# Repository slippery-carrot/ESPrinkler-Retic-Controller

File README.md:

# 🌱 ESPrinkler Retic Controller

An open-source, ESP32-based smart irrigation controller built with **ESPHome** and designed for seamless integration with **Home Assistant**.

ESPrinkler gives you full local control over your irrigation system—no cloud services, no subscriptions, and no reliance on external servers. All schedules are stored directly on the device, ensuring your system continues to run even if Home Assistant or network connectivity becomes unavailable.

---

## 🚀 Features

- Fully local operation (no cloud dependencies)  
- Home Assistant integration via ESPHome  
- Standalone operation with onboard schedule storage  
- Solid-state design with optically isolated outputs  
- Control up to **8 irrigation zones + pump/master valve**  
- Support for **up to 3 independent watering programs**  
- Flexible scheduling:
  - Day-of-week control  
  - Up to 4 start times per program  
  - Configurable zone durations and repeat cycles  
- LED indicators for system status and outputs  

---

## 🧠 How It Works

ESPrinkler operates using up to **three independent watering programs**, each of which defines:

- When watering occurs (days + start times)  
- Which zones are active  
- How long each zone runs  
- Whether the cycle repeats  

All configuration is done through **Home Assistant entities**, and once configured, the controller runs autonomously.

⚠️ Programs **do not prevent overlap automatically**, so you must ensure schedules don’t conflict.

---

## 🏗️ Hardware Overview

The controller is built around an **ESP32 (ESP32-DevKitC compatible)** and a custom PCB designed for irrigation control.

Key hardware characteristics:

- Compatible with 24VAC reticulation systems
- Solid-state solenoid switching  
- Isolated AC/DC sections
- Fused solenoid power output
- Terminal block wiring for:
  - Power input  
  - Pump/master valve  
  - 8 irrigation zones  
- Optional external LEDs for:
  - Wi-Fi status  
  - System status  

For full specifications, wiring diagrams, and pinouts, see:  
**[Hardware Specifications Wiki](../../wiki/Hardware-Specifications)**

---

## ⚡ Requirements

To build and use ESPrinkler, you’ll need:

- ESP32 Dev Board (ESP32-DevKitC compatible)  
- ESPrinkler PCB (assembled or DIY)  
- 24VAC transformer (~30VA recommended)  
- Fuse (M205 1A Quick Blow)  
- Suitable enclosure  
- Wiring/connectors for your installation  
- Home Assistant with ESPHome installed  

---

## 🛠️ Getting Started

### 1. Set Up ESPHome

Install and configure ESPHome in Home Assistant:  
https://esphome.io/guides/getting_started_hassio/

---

### 2. Prepare Firmware

- Copy the provided `secrets.yaml` values into your ESPHome setup  
- Import the `retic-controller.yaml` file into ESPHome (Add new device -> Import from file) 
- Update the substitutions (Wi-Fi, API key, device name, etc.)  

---

### 3. Flash the Device

- Click the 3 dots under the new configuration
- Click "install" and follow your preferred method to flash your ESP32
- I recommend choosing "manual download" and then navigate to [ESPHome Web](https://web.esphome.io/) to flash your device using the binary file
- Once flashed, the device will appear in Home Assistant

---

### 4. Wire the Hardware

- Connect 24VAC input  
- Connect solenoids (zones + common)  
- Install fuse  
- Optional: connect status LEDs  

⚠️ **Warning:** This involves working with mains/low-voltage AC systems. Follow all relevant electrical safety standards and regulations.
👉 See the **[Hardware Specifications Wiki](../../wiki/Hardware-Specifications)** for full wiring details and pinouts.

---

### 5. Configure in Home Assistant

Once the device is online:

- Enable one or more programs  
- Set watering days  
- Configure start times  
- Enable zones and durations
- An example [dashboard page .yaml file](https://github.com/slippery-carrot/ESPrinkler-Retic-Controller/blob/main/ESPHome/ESPrinkler_Dashboard_Example.yaml) has been provided as an example layout in Home Assistant

⚠️ **NOTE:** The example dashboard yaml uses [Mushroom Cards](https://github.com/piitaya/lovelace-mushroom), so make sure to install that if you want it to function.
👉 See the **[Home Assistant Entities Wiki](../../wiki/Home-Assistant-Entities)** for a full breakdown of all controls, sensors, and configuration options.

---

## 🌿 Program Basics

Each program requires:

- ✅ Program enabled  
- ✅ At least one watering day  
- ✅ At least one start time  
- ✅ At least one active zone with duration  

Optional settings:

- Repeat cycles (repeat full zone sequence)  

---

## 🏠 Home Assistant Integration

ESPrinkler exposes a full set of:

- **Controls** (start/stop, enable program, pause)  
- **Sensors** (current zone, time remaining, next cycle)  
- **Configuration entities** (days, times, durations, repeats)  
- **Diagnostics** (Wi-Fi signal, uptime, firmware, etc.)  

👉 Full details here:  
**[Home Assistant Entities Wiki](../../wiki/Home-Assistant-Entities)**

---

## 🧩 Project Structure

- Firmware: ESPHome YAML configuration and secrets example, including example dashboard layout  
- Hardware: Custom PCB design in KiCad and production files
- Documentation:
  - README (this file)  
  - Hardware Wiki  
  - Home Assistant Wiki  

---

## ⚠️ Important Notes

- Programs **can overlap** if configured incorrectly—this is not automatically prevented  
- Default start times may be active—always verify configuration  
- Ensure the transformer you choose is correctly sized for your solenoid load
- Always use appropriate fuse protection

---

## 🪰 Limitations, Issues, and Bugs
 - ESPrinkler requires connection to home assistant at least once in order to set its internal clock. Without this, it has no reference to the current time and date

## 🔗 Documentation

- 📘 **[Hardware Specifications Wiki](../../wiki/Hardware-Specifications)** – Pinouts, wiring, electrical specs  
- 📗 **[Home Assistant Entities Wiki](../../wiki/Home-Assistant-Entities)** – Entities, controls, automation  

---

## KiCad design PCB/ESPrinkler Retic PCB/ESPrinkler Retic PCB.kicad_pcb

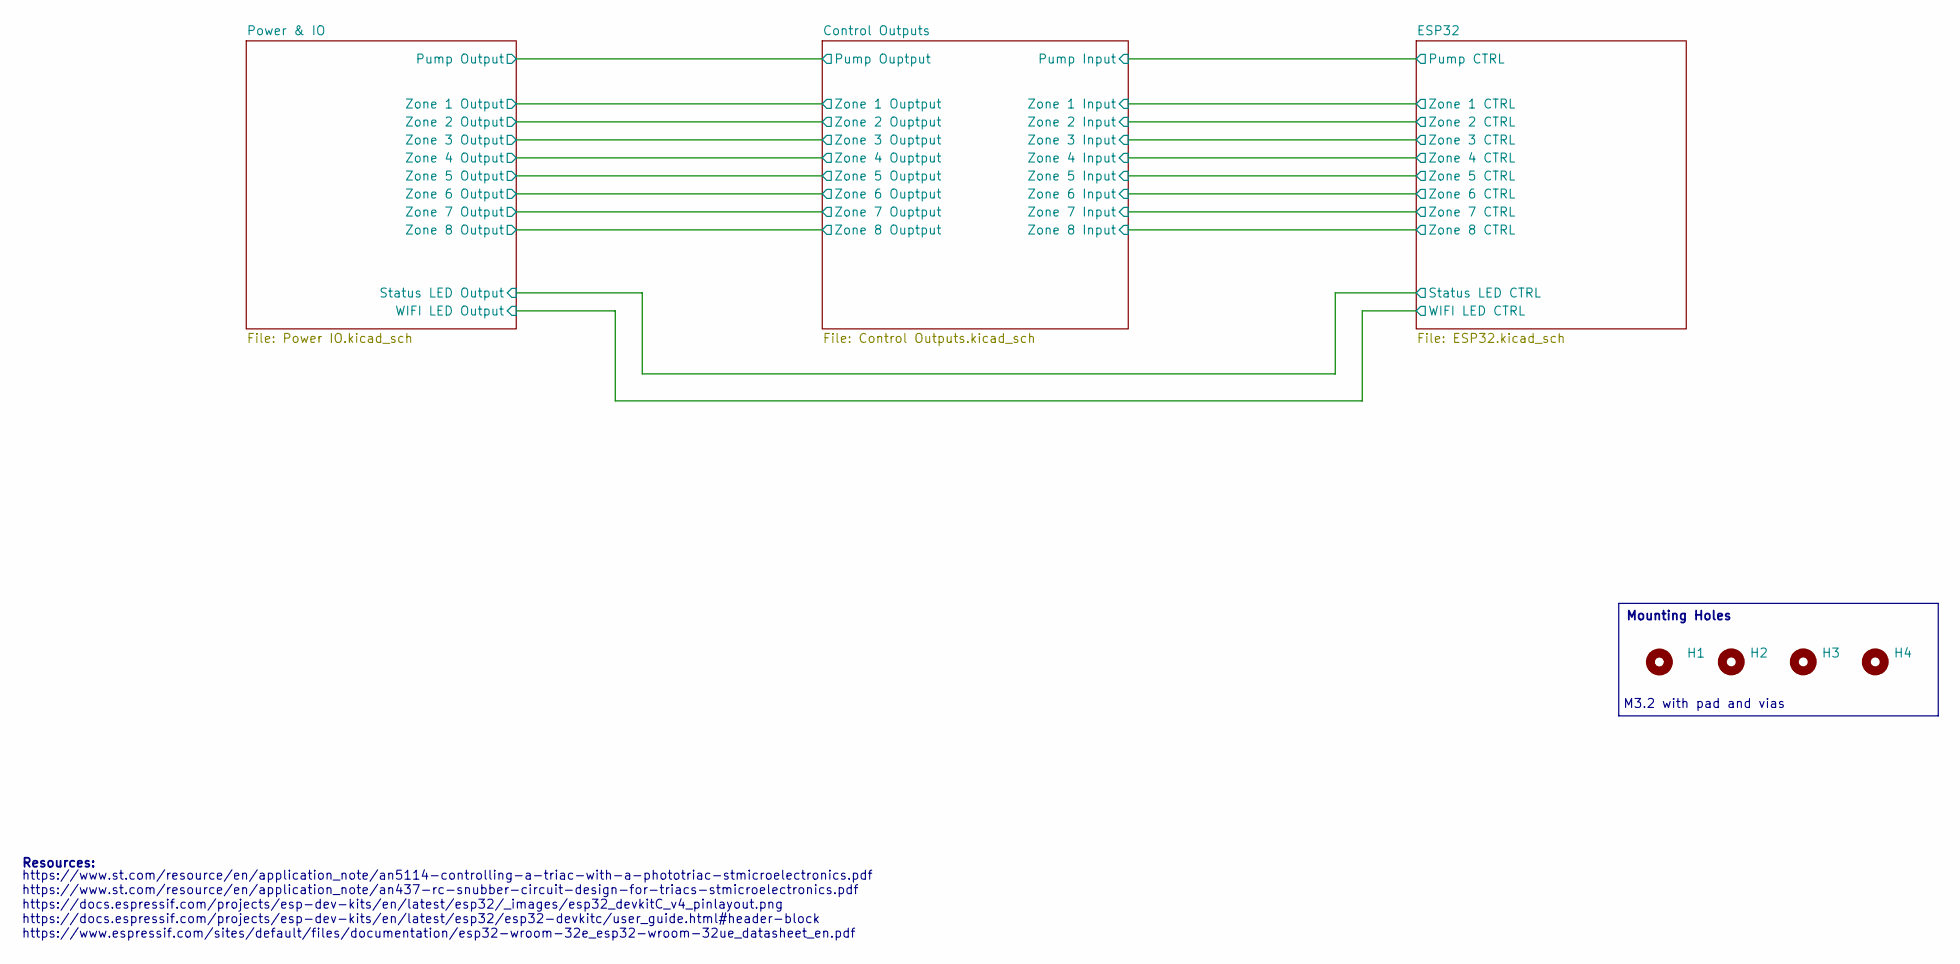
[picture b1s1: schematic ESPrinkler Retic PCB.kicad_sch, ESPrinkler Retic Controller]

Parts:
H1, H2, H3, H4: MountingHole; MountingHole_3.2mm_M3_Pad_Via

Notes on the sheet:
https://www.st.com/resource/en/application_note/an5114-controlling-a-triac-with-a-phototriac-stmicroelectronics.pdf https://www.st.com/resource/en/application_note/an437-rc-snubber-circuit-design-for-triacs-stmicroelectronics.pdf https://docs.espressif.com/projects/esp-dev-kits/en/latest/esp32/_ima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
M3.2 with pad and vias
Resources:
Mounting Holes

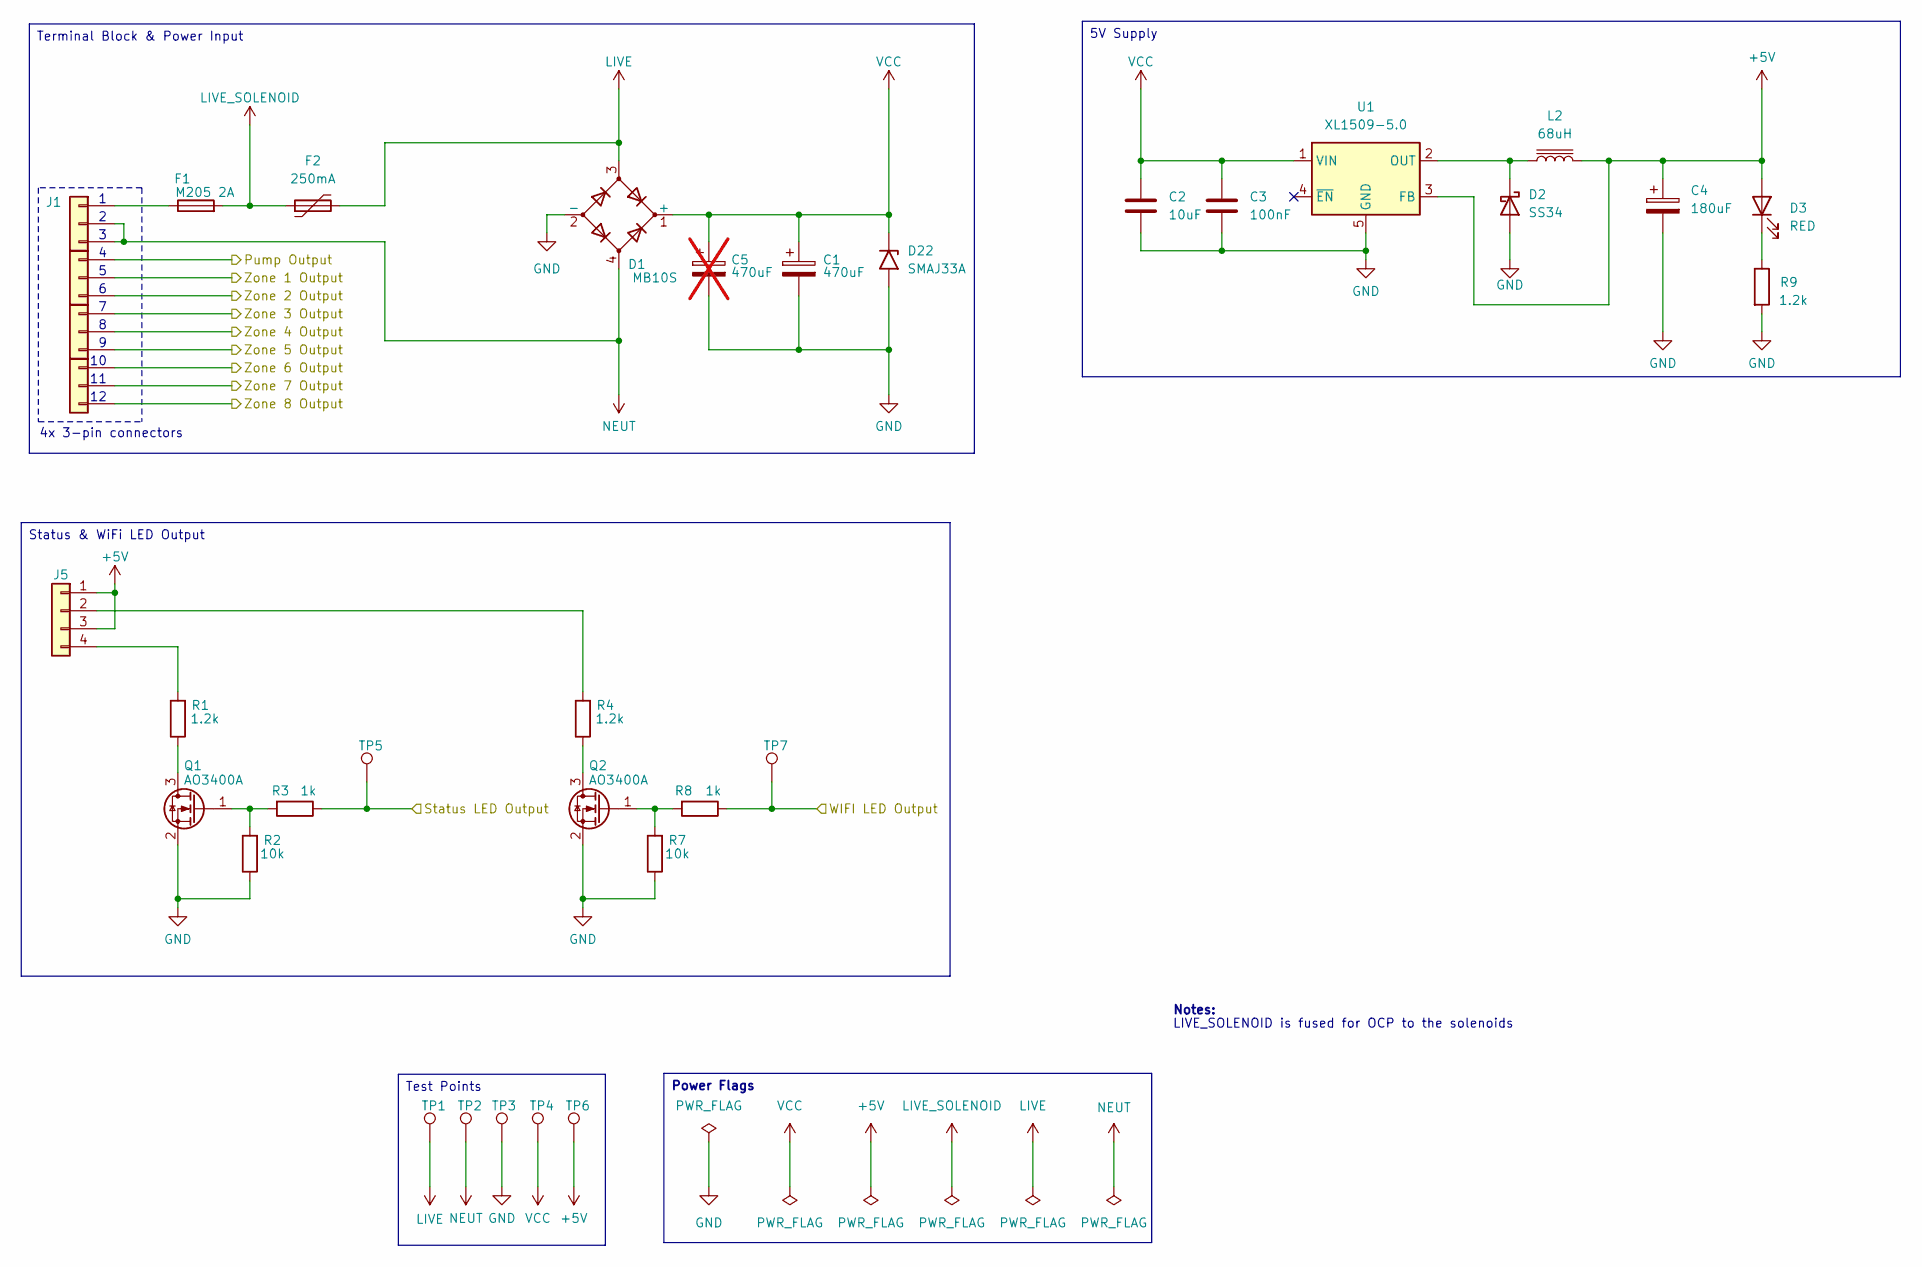
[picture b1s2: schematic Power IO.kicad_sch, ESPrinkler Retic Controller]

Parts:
C1: 470uF; CP_Radial_D10.0mm_P5.00mm; Manufacturer P/N PA63V470M10X17
C2: 10uF; C_1206_3216Metric; Manufacturer P/N CL31A106KBHNNNE
C3: 100nF; C_0805_2012Metric; Manufacturer P/N CL21B104KCFNNNE
C4: 180uF; CP_Radial_D6.3mm_P2.50mm; Manufacturer P/N PA25V180M6X7
C5: 470uF; CP_Radial_D10.0mm_P5.00mm; Manufacturer P/N PA63V470M10X17; not fitted
D1: MB10S; OnSemi_751EP_SOIC-4_3.9x4.725mm_P2.54mm; Manufacturer P/N MB10S-50MIL
D2: SS34; D_SMA; Manufacturer P/N SS34
D3: RED; LED_0603_1608Metric; Manufacturer P/N KT-0603R
D22: SMAJ33A; D_SMA; Manufacturer P/N SMAJ33A
F1: M205 2A; Fuseholder_Cylinder-5x20mm_Schurter_0031_8201_Horizontal_Op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; Manufacturer P/N PTF-15
F2: 250mA; Fuse_BelFuse_0ZRE0033FF_L11.4mm_W3.8mm; Manufacturer P/N RLVR240-025
J1, J2, J3, J4: DB910-7.62-3P-GN-S; DORABO_DB910-7.62-3P-GN-S_1x03_P7.62mm_Vertical; Manufacturer P/N DB910-7.62-3P-GN-S
J5: Conn_01x04; TerminalBlock_Phoenix_PT-1,5-4-5.0-H_1x04_P5.00mm_Horizontal; Manufacturer P/N DB301V-5.0-4P-BU-S
L2: 68uH; L_APV_ANR5045; Manufacturer P/N SMNR5040-680MT
Q1, Q2: AO3400A; SOT-23_Handsoldering; Manufacturer P/N AO3400A
R1, R4, R9: 1.2k; R_0805_2012Metric; Manufacturer P/N 0805W8F1201T5E
R2, R7: 10k; R_0805_2012Metric; Manufacturer P/N 0805W8F1002T5E
R3, R8: 1k; R_0805_2012Metric; Manufacturer P/N 0805W8F1001T5E
TP1, TP2, TP3, TP4, TP5, TP6, TP7: TestPoint; TestPoint_Pad_D1.5mm; Manufacturer P/N N/A
U1: XL1509-5.0; SOIC-8_3.9x4.9mm_P1.27mm; Manufacturer P/N XL1509-5.0E1

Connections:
+5V: C4.1, D3.2 (A), J5.1, J5.3, L2.2, TP6.1 (1_1), U1.3 (FB); also elsewhere on the board
/Control Outputs/Pump Ouptput: J2.1; also elsewhere on the board
/Control Outputs/Zone 1 Ouptput: J2.2; also elsewhere on the board
/Control Outputs/Zone 2 Ouptput: J2.3; also elsewhere on the board
/Control Outputs/Zone 3 Ouptput: J3.1; also elsewhere on the board
/Control Outputs/Zone 4 Ouptput: J3.2; also elsewhere on the board
/Control Outputs/Zone 5 Ouptput: J3.3; also elsewhere on the board
/Control Outputs/Zone 6 Ouptput: J4.1; also elsewhere on the board
/Control Outputs/Zone 7 Ouptput: J4.2; also elsewhere on the board
/Control Outputs/Zone 8 Ouptput: J4.3; also elsewhere on the board
/ESP32/Status LED CTRL: R3.1, TP5.1 (1_1); also elsewhere on the board
/ESP32/WIFI LED CTRL: R8.1, TP7.1 (1_1); also elsewhere on the board
GND: C1.2, C2.2, C3.1, C4.2, C5.2, D1.2 (-), D2.2 (A), D22.2 (A2), Q1.2 (S), Q2.2 (S), R2.1, R7.1, R9.2, TP3.1 (1_1), U1.5 (GND), U1.6 (GND), U1.7 (GND), U1.8 (GND); also elsewhere on the board
LIVE: D1.3, F2.2, TP1.1 (1_1)
LIVE_SOLENOID: F1.2, F2.1; also elsewhere on the board
NEUT: D1.4, J1.2, J1.3, TP2.1 (1_1); also elsewhere on the board
unnamed: D2.1 (K), L2.1, U1.2 (OUT)
unnamed: D3.1 (K), R9.1
unnamed: F1.1, J1.1
unnamed: J5.2, R4.2
unnamed: J5.4, R1.2
unnamed: Q1.3 (D), R1.1
unnamed: Q1.1 (G), R2.2, R3.2
unnamed: Q2.3 (D), R4.1
unnamed: Q2.1 (G), R7.2, R8.2
VCC: C1.1, C2.1, C3.2, C5.1, D1.1 (+), D22.1 (A1), TP4.1 (1_1), U1.1 (VIN)

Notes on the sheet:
4x 3-pin connectors
LIVE_SOLENOID is fused for OCP to the solenoids
Notes:
Status & WiFi LED Output
Test Points
Terminal Block & Power Input
5V Supply
Power Flags

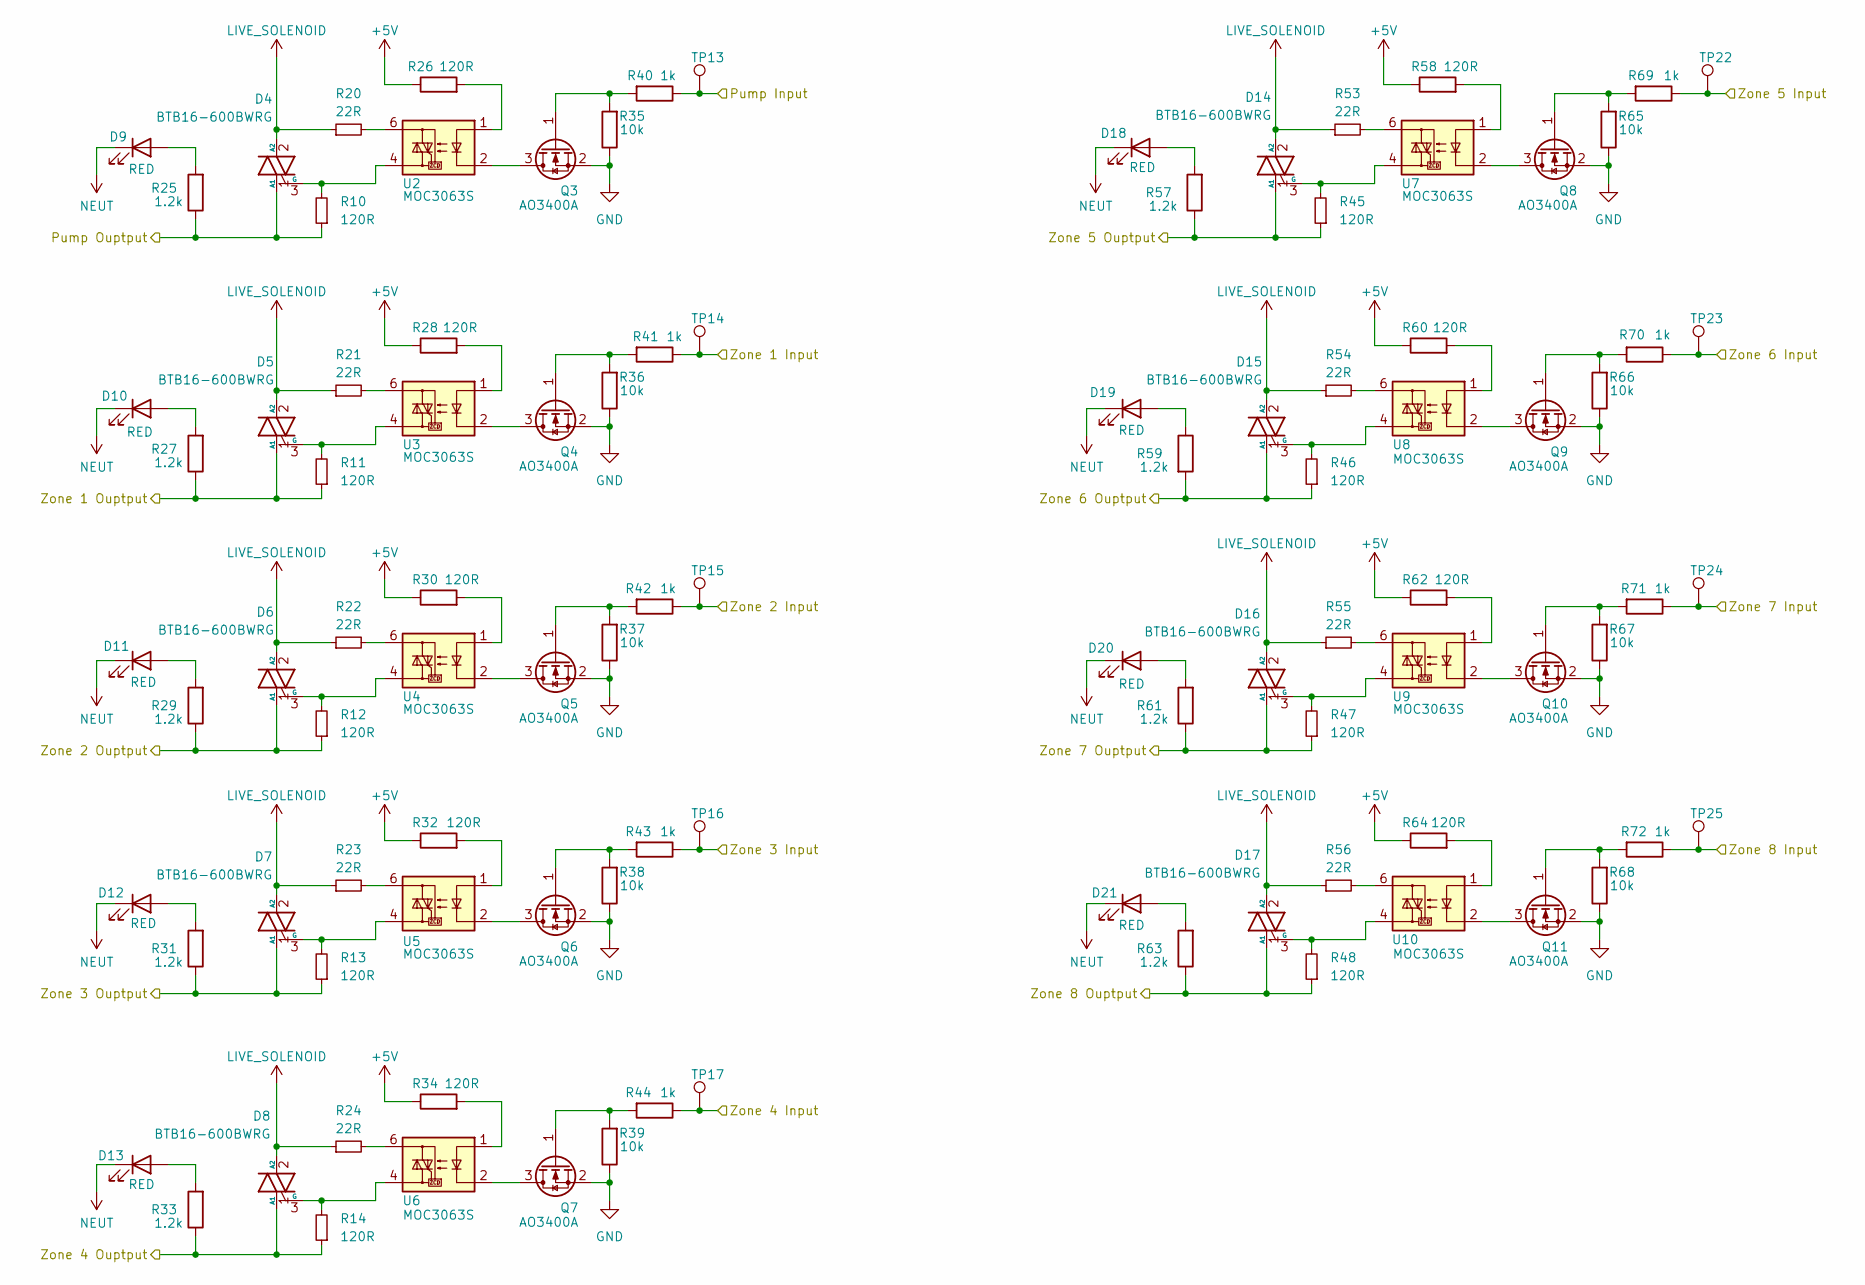
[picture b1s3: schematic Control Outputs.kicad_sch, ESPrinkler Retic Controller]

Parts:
D4, D5, D6, D7, D8, D14, D15, D16, D17: BTB16-600BWRG; TO-220-3_Horizontal_TabDown_NoHole; Manufacturer P/N BTB16-600BWRG
D9, D10, D11, D12, D13, D18, D19, D20, D21: RED; LED_0603_1608Metric; Manufacturer P/N KT-0603R
Q3, Q4, Q5, Q6, Q7, Q8, Q9, Q10, Q11: AO3400A; SOT-23_Handsoldering; Manufacturer P/N AO3400A
R10, R11, R12, R13, R14, R26, R28, R30, R32, R34, R45, R46, R47, R48, R58, R60, R62, R64: 120R; R_0805_2012Metric; Manufacturer P/N 0805W8F1200T5E
R20, R21, R22, R23, R24, R53, R54, R55, R56: 22R; R_0805_2012Metric; Manufacturer P/N 0805W8F220JT5E
R25, R27, R29, R31, R33, R57, R59, R61, R63: 1.2k; R_0805_2012Metric; Manufacturer P/N 0805W8F1201T5E
R35, R36, R37, R38, R39, R65, R66, R67, R68: 10k; R_0805_2012Metric; Manufacturer P/N 0805W8F1002T5E
R40, R41, R42, R43, R44, R69, R70, R71, R72: 1k; R_0805_2012Metric; Manufacturer P/N 0805W8F1001T5E
TP13, TP14, TP15, TP16, TP17, TP22, TP23, TP24, TP25: TestPoint; TestPoint_Pad_D1.5mm; Manufacturer P/N N/A
U2, U3, U4, U5, U6, U7, U8, U9, U10: MOC3063S; MOC306XS_LTO; Manufacturer P/N MOC3063S-TA1

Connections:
+5V: R26.1, R28.1, R30.1, R32.1, R34.1, R58.1, R60.1, R62.1, R64.1; also elsewhere on the board
/Control Outputs/Pump Input: R40.1, TP13.1 (1_1); also elsewhere on the board
/Control Outputs/Pump Ouptput: D4.1 (A1), R10.1, R25.1; also elsewhere on the board
/Control Outputs/Zone 1 Input: R41.1, TP14.1 (1_1); also elsewhere on the board
/Control Outputs/Zone 1 Ouptput: D5.1 (A1), R11.1, R27.1; also elsewhere on the board
/Control Outputs/Zone 2 Input: R42.1, TP15.1 (1_1); also elsewhere on the board
/Control Outputs/Zone 2 Ouptput: D6.1 (A1), R12.1, R29.1; also elsewhere on the board
/Control Outputs/Zone 3 Input: R43.1, TP16.1 (1_1); also elsewhere on the board
/Control Outputs/Zone 3 Ouptput: D7.1 (A1), R13.1, R31.1; also elsewhere on the board
/Control Outputs/Zone 4 Input: R44.1, TP17.1 (1_1); also elsewhere on the board
/Control Outputs/Zone 4 Ouptput: D8.1 (A1), R14.1, R33.1; also elsewhere on the board
/Control Outputs/Zone 5 Input: R69.1, TP22.1 (1_1); also elsewhere on the board
/Control Outputs/Zone 5 Ouptput: D14.1 (A1), R45.1, R57.1; also elsewhere on the board
/Control Outputs/Zone 6 Input: R70.1, TP23.1 (1_1); also elsewhere on the board
/Control Outputs/Zone 6 Ouptput: D15.1 (A1), R46.1, R59.2; also elsewhere on the board
/Control Outputs/Zone 7 Input: R71.1, TP24.1 (1_1); also elsewhere on the board
/Control Outputs/Zone 7 Ouptput: D16.1 (A1), R47.1, R61.1; also elsewhere on the board
/Control Outputs/Zone 8 Input: R72.1, TP25.1 (1_1); also elsewhere on the board
/Control Outputs/Zone 8 Ouptput: D17.1 (A1), R48.1, R63.1; also elsewhere on the board
GND: Q3.2 (S), Q4.2 (S), Q5.2 (S), Q6.2 (S), Q7.2 (S), Q8.2 (S), Q9.2 (S), Q10.2 (S), Q11.2 (S), R35.1, R36.1, R37.1, R38.1, R39.1, R65.1, R66.1, R67.1, R68.1; also elsewhere on the board
LIVE_SOLENOID: D4.2 (A2), D5.2 (A2), D6.2 (A2), D7.2 (A2), D8.2 (A2), D14.2 (A2), D15.2 (A2), D16.2 (A2), D17.2 (A2), R20.1, R21.1, R22.1, R23.1, R24.1, R53.1, R54.1, R55.1, R56.1; also elsewhere on the board
NEUT: D9.1 (K), D10.1 (K), D11.1 (K), D12.1 (K), D13.1 (K), D18.1 (K), D19.1 (K), D20.1 (K), D21.1 (K); also elsewhere on the board
unnamed: D4.3 (G), R10.2, U2.4
unnamed: D5.3 (G), R11.2, U3.4
unnamed: D6.3 (G), R12.2, U4.4
unnamed: D7.3 (G), R13.2, U5.4
unnamed: D8.3 (G), R14.2, U6.4
unnamed: D9.2 (A), R25.2
unnamed: D10.2 (A), R27.2
unnamed: D11.2 (A), R29.2
unnamed: D12.2 (A), R31.2
unnamed: D13.2 (A), R33.2
unnamed: D14.3 (G), R45.2, U7.4
unnamed: D15.3 (G), R46.2, U8.4
unnamed: D16.3 (G), R47.2, U9.4
unnamed: D17.3 (G), R48.2, U10.4
unnamed: D18.2 (A), R57.2
unnamed: D19.2 (A), R59.1
unnamed: D20.2 (A), R61.2
unnamed: D21.2 (A), R63.2
unnamed: Q3.3 (D), U2.2
unnamed: Q3.1 (G), R35.2, R40.2
unnamed: Q4.3 (D), U3.2
unnamed: Q4.1 (G), R36.2, R41.2
unnamed: Q5.3 (D), U4.2
unnamed: Q5.1 (G), R37.2, R42.2
unnamed: Q6.3 (D), U5.2
unnamed: Q6.1 (G), R38.2, R43.2
unnamed: Q7.3 (D), U6.2
unnamed: Q7.1 (G), R39.2, R44.2
unnamed: Q8.3 (D), U7.2
unnamed: Q8.1 (G), R65.2, R69.2
unnamed: Q9.3 (D), U8.2
unnamed: Q9.1 (G), R66.2, R70.2
unnamed: Q10.3 (D), U9.2
unnamed: Q10.1 (G), R67.2, R71.2
unnamed: Q11.3 (D), U10.2
unnamed: Q11.1 (G), R68.2, R72.2
unnamed: R20.2, U2.6
unnamed: R21.2, U3.6
unnamed: R22.2, U4.6
unnamed: R23.2, U5.6
unnamed: R24.2, U6.6
unnamed: R26.2, U2.1
unnamed: R28.2, U3.1
unnamed: R30.2, U4.1
unnamed: R32.2, U5.1
unnamed: R34.2, U6.1
unnamed: R53.2, U7.6
unnamed: R54.2, U8.6
unnamed: R55.2, U9.6
unnamed: R56.2, U10.6
unnamed: R58.2, U7.1
unnamed: R60.2, U8.1
unnamed: R62.2, U9.1
unnamed: R64.2, U10.1

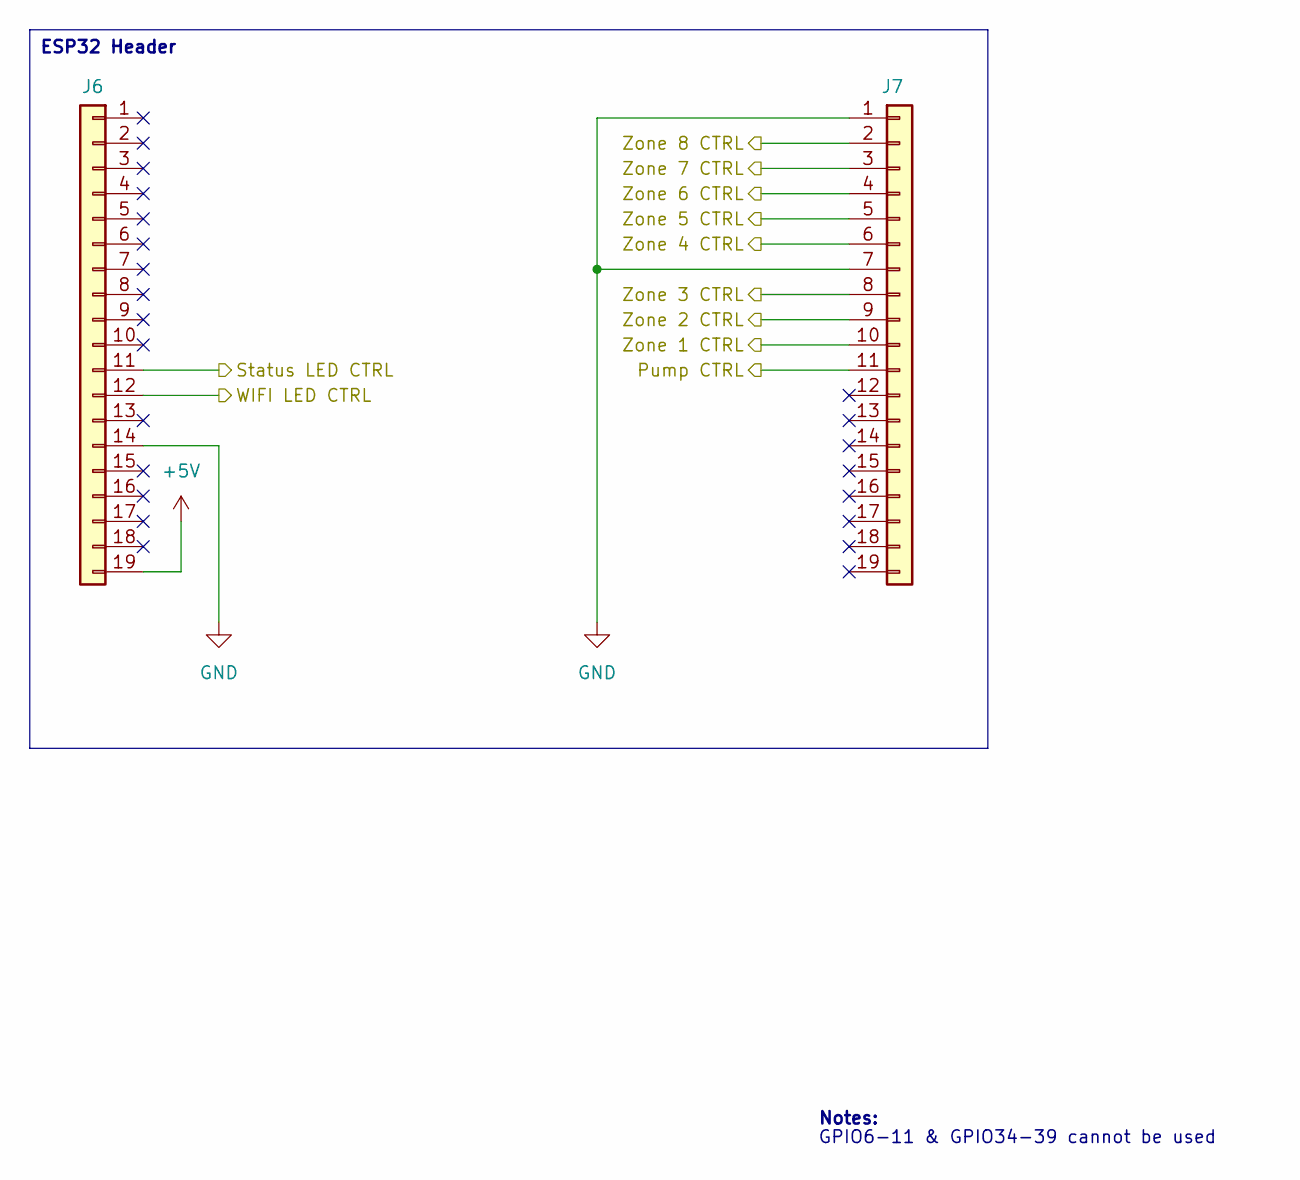
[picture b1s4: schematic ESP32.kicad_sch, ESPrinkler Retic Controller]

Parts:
J6, J7: Conn_01x19; PinSocket_1x19_P2.54mm_Vertical; Manufacturer P/N KH-2.54FH-1X19P-H8.5

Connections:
+5V: J6.19; also elsewhere on the board
/Control Outputs/Pump Input: J7.11; also elsewhere on the board
/Control Outputs/Zone 1 Input: J7.10; also elsewhere on the board
/Control Outputs/Zone 2 Input: J7.9; also elsewhere on the board
/Control Outputs/Zone 3 Input: J7.8; also elsewhere on the board
/Control Outputs/Zone 4 Input: J7.6; also elsewhere on the board
/Control Outputs/Zone 5 Input: J7.5; also elsewhere on the board
/Control Outputs/Zone 6 Input: J7.4; also elsewhere on the board
/Control Outputs/Zone 7 Input: J7.3; also elsewhere on the board
/Control Outputs/Zone 8 Input: J7.2; also elsewhere on the board
/ESP32/Status LED CTRL: J6.11; also elsewhere on the board
/ESP32/WIFI LED CTRL: J6.12; also elsewhere on the board
GND: J6.14, J7.1, J7.7; also elsewhere on the board

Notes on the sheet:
GPIO6-11 & GPIO34-39 cannot be used
Notes:
ESP32 Header

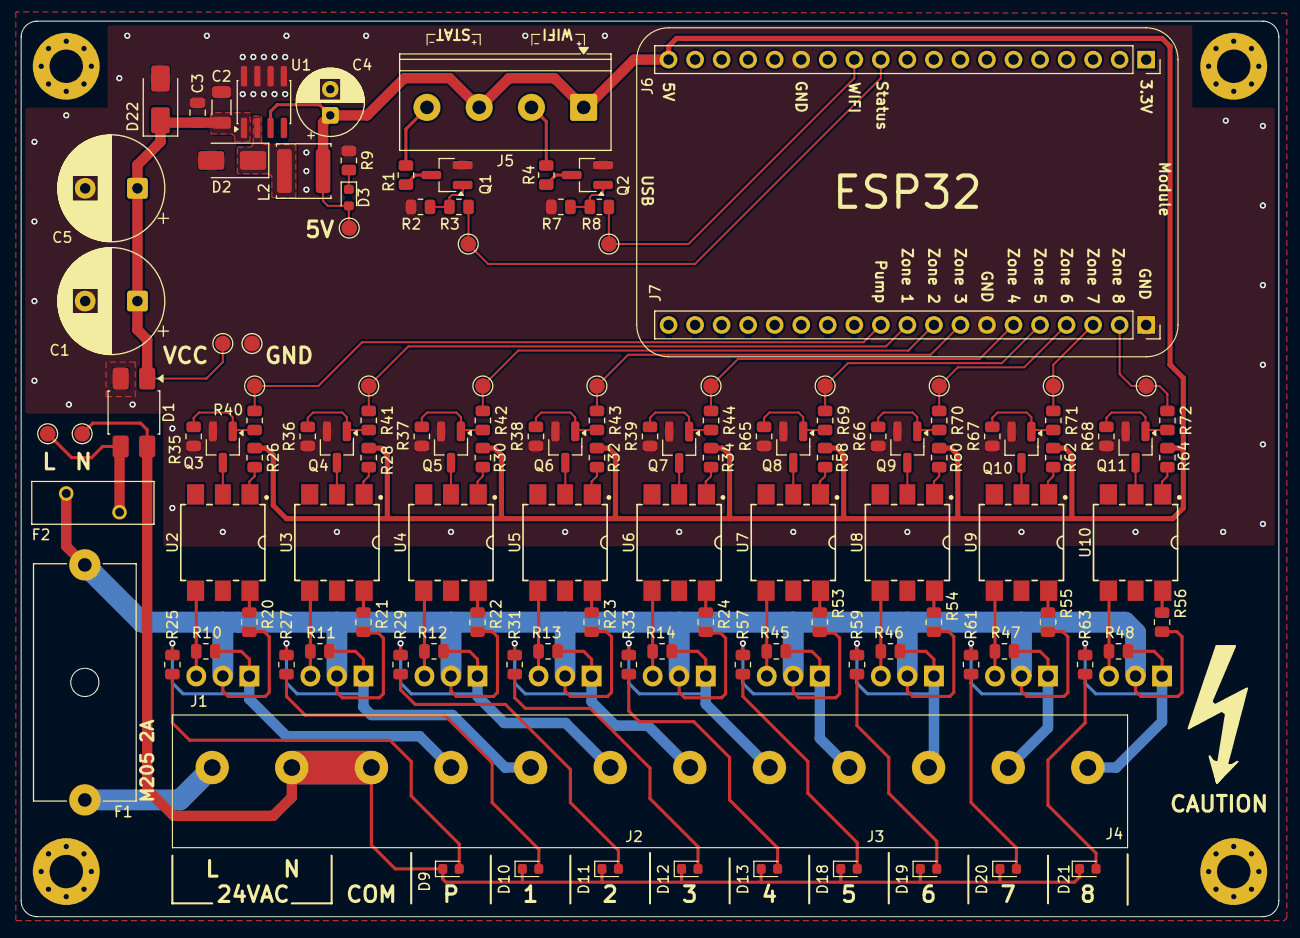
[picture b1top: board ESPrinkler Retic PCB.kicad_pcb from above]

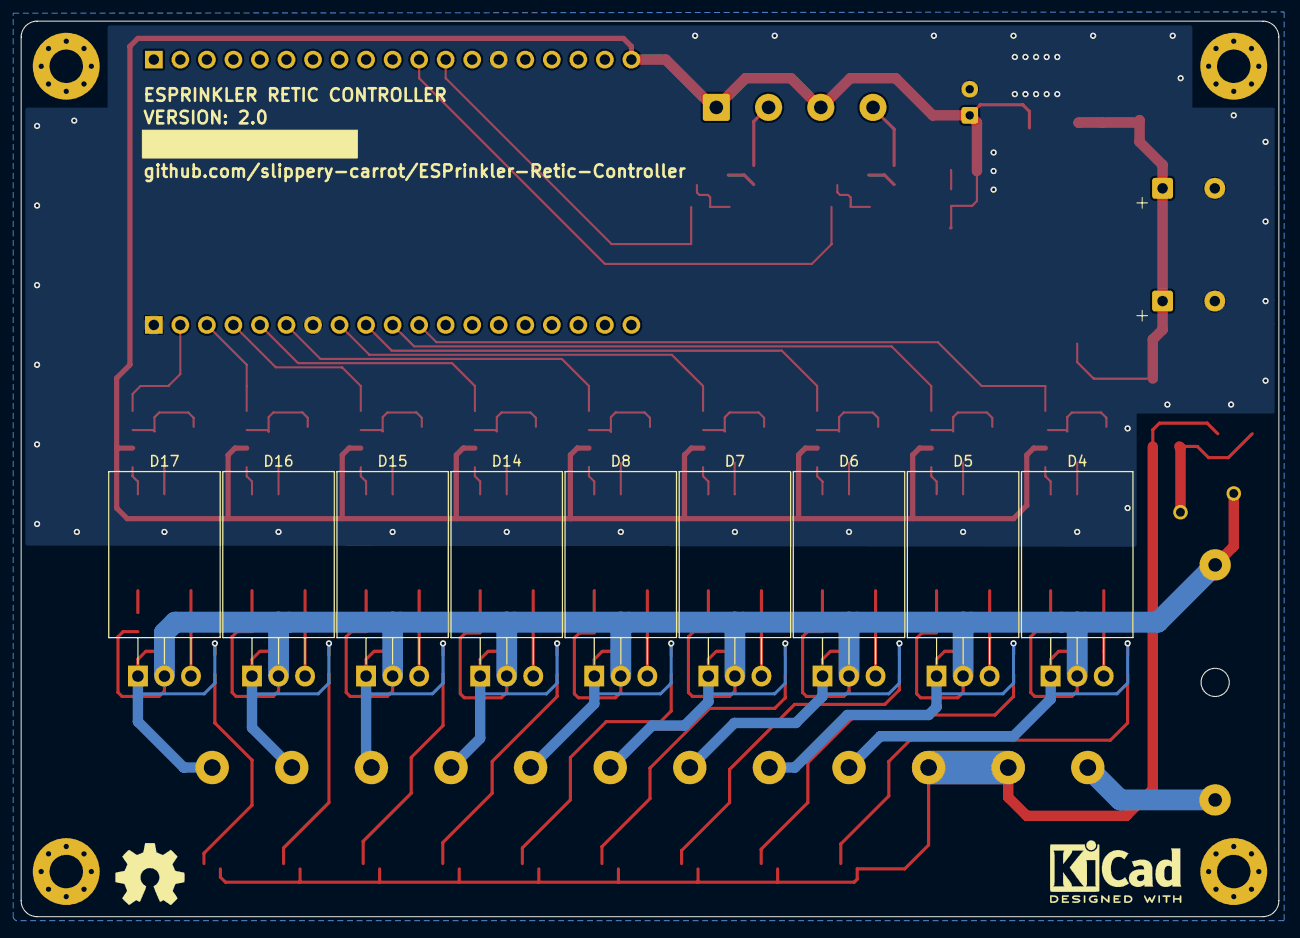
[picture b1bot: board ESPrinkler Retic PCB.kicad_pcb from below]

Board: 2 copper layers, 120.4 x 85.7 mm, 139 parts (9 on the bottom side), 89 nets.

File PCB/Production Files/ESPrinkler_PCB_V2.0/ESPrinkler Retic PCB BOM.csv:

Reference,Value,Supplier,Supplier P/N,Manufacturer,Manufacturer P/N,Footprint,Qty,DNP
C1,680uF,LCSC,C26225,CX(Dongguan Chengxing Elec),GR687M050J20RR0VH4FP0,Capacitor_THT:CP_Radial_D13.0mm_P5.00mm,1,
C2,10uF,LCSC,C13585,Samsung Electro-Mechanics,CL31A106KBHNNNE,Capacitor_SMD:C_1206_3216Metric,1,
C3,100nF,LCSC,C28233,Samsung Electro-Mechanics,CL21B104KCFNNNE,Capacitor_SMD:C_0805_2012Metric,1,
C4,180uF,LCSC,C442817,Ymin,LKMC0901E181MF,Capacitor_THT:CP_Radial_D6.3mm_P2.50mm,1,
D1,MB10S,LCSC,C2488, MDD(Microdiode Semiconductor),MB10S-50MIL ,Footprints:OnSemi_751EP_SOIC-4_3.9x4.725mm_P2.54mm,1,
D2,SS34,LCSC,C8678,MDD(Microdiode Semiconductor),SS34,Diode_SMD:D_SMA,1,
"D3,D9,D10,D11,D12,D13,D18,D19,D20,D21",RED,LCSC,C2286,Hubei KENTO Elec,KT-0603R,LED_SMD:LED_0603_1608Metric,10,
"D4,D5,D6,D7,D8,D14,D15,D16,D17",BTB16-600BWRG,LCSC,C669873,STMicroelectronics,BTB16-600BWRG,Footprints:TO-220-3_Horizontal_TabDown_NoHole,9,
D22,SMAJ33A,LCSC,C223988,Littelfuse ,SMAJ33A,Diode_SMD:D_SMA,1,
F1,M205 2A,LCSC,C842712,XFCN,PTF-15,Fuse:Fuseholder_Cylinder-5x20mm_Schurter_0031_8201_Horizontal_Open,1,
F2,250mA,LCSC,C20871,RUILON(Shenzhen Ruilongyuan Elec),RLVR240-025,Fuse:Fuse_BelFuse_0ZRE0033FF_L11.4mm_W3.8mm,1,
"J1,J2,J3,J4",DB910-7.62-3P-GN-S,LCSC,C395877,DORABO,DB910-7.62-3P-GN-S,Footprints:DORABO_DB910-7.62-3P-GN-S_1x03_P7.62mm_Vertical,4,
J5,Conn_01x04,LCSC,C3034542,DORABO,DB301V-5.0-4P-BU-S,"TerminalBlock_Phoenix:TerminalBlock_Phoenix_PT-1,5-4-5.0-H_1x04_P5.00mm_Horizontal",1,
"J6,J7",Conn_01x19,LCSC,C2932678,Shenzhen Kinghelm Elec,KH-2.54FH-1X19P-H8.5,Connector_PinSocket_2.54mm:PinSocket_1x19_P2.54mm_Vertical,2,
L2,68uH,LCSC,C9393,SXN(Shun Xiang Nuo Elec),SMNR5040-680MT,Inductor_SMD:L_APV_ANR5045,1,
"Q1,Q2,Q3,Q4,Q5,Q6,Q7,Q8,Q9,Q10,Q11",AO3400A,LCSC,C20917,Alpha & Omega Semicon,AO3400A,Package_TO_SOT_SMD:SOT-23_Handsoldering,11,
"R1,R4,R9,R25,R27,R29,R31,R33,R57,R59,R61,R63",1.2k,LCSC,C17379,UNI-ROYAL(Uniroyal Elec),0805W8F1201T5E,Resistor_SMD:R_0805_2012Metric,12,
"R2,R7,R35,R36,R37,R38,R39,R65,R66,R67,R68",10k,LCSC,C17414,UNI-ROYAL(Uniroyal Elec),0805W8F1002T5E,Resistor_SMD:R_0805_2012Metric,11,
"R3,R8,R40,R41,R42,R43,R44,R69,R70,R71,R72",1k,LCSC,C17513,UNI-ROYAL(Uniroyal Elec),0805W8F1001T5E,Resistor_SMD:R_0805_2012Metric,11,
"R10,R11,R12,R13,R14,R26,R28,R30,R32,R34,R45,R46,R47,R48,R58,R60,R62,R64",120R,LCSC,C17437,UNI-ROYAL(Uniroyal Elec),0805W8F1200T5E,Resistor_SMD:R_0805_2012Metric,18,
"R20,R21,R22,R23,R24,R53,R54,R55,R56",22R,LCSC,C17561,UNI-ROYAL(Uniroyal Elec),0805W8F220JT5E,Resistor_SMD:R_0805_2012Metric,9,
U1,XL1509-5.0,LCSC,C61063,XLSEMI,XL1509-5.0E1,Package_SO:SOIC-8_3.9x4.9mm_P1.27mm,1,
"U2,U3,U4,U5,U6,U7,U8,U9,U10",MOC3063S,LCSC,C77950,Lite-On,MOC3063S-TA1,Footprints:MOC306XS_LTO,9,

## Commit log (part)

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2025-02-19 Begin setup of repo, add folders, create PCB project, add YAML file
2025-02-24 Begin work on PCB design
2025-02-25 Choose parts for components
2025-02-28 Continue with parts selection for components
2025-03-05 Remove part choices due to schematic setup issue, will redo this at some point.
    Add headers for ESP32
2025-03-06 Added code to control a Wifi status LED and a general status LED.
    Added above onto schematic, start working on ESP32 dev kit pinout
2025-03-10 Begin muilti-sheet design to organise schematic better
2025-03-16 Continue migrating PCB project to multi sheet design
2025-03-16 Continued work migrating to multi-sheet design
2025-03-17 Lay out control schematic and begin choosing parts
    Source parts for existing symbols on the control schematic after laying out pump and zone circuits
2025-03-17 Continue parts sourcing for existing components
    Continue to source parts from LCSC for the existing components.
2025-03-22 Initial schematic design completed
    Finish initial schematic design and source all required components. DRC completed with only minor warnings (regarding net names, no worries). Move on to begin PCB design
2025-03-22 Begin work on PCB
2025-03-24 Update file to suit PCB
    Changed GPIOs for solenoids, change relay inversion to false
2025-03-24 Begin PCB layout
    Need to find a better connector for power and outputs
2025-03-24 Remove commented out API section
2025-03-24 Attempting to source different 12 pin connector
2025-04-02 Found potential solution for main header connector
    Choose main header solution, create footprint for header, update SCH and PCB
2025-04-02 Add web server component
2025-04-07 PCB and SCH work
    Fix symbol issue for mosfet.
    Continue PCB design layout
2025-04-26 Continued work on PCB development
2025-05-04 Continue PCB design
    Change footprint of triacs to include solder tab for securing package to PCB and heat dissipation.
    Change footprint of optocoupler for better solder mask outlines and smaller pads.
2025-05-18 Change LED output indicator
    Change LED indication for each channel to be powered off 24VAC line post triac instead of off the MOSFET. Easier PCB design and effectively same result
2025-05-19 Continue PCB layout
    Final placements and traces of components for first revision.
2025-05-31 Modify SCH
    Remote ~ from datasheet section and spelling mistake on parts list.
    Swap status and wifi led control GPIOs for easier PCB traces
2025-05-31 PCB touch ups
    Add more detail to PCB.
    Clean up traces.
    Add 3D model for full bridge rectifier.
2025-06-09 Update Schematics
    For all, update title block information.
    Power IO:
    - Change PTC fuse footprint reference
    - Add part info for J1
    Control Outputs:
    - Add notes and box areas of schematic for clarity
2025-06-09 Export SCH as PDF
2025-06-09 Modify PCB layout & Export MFG files
    Modified PCB layout after exporting mfg files and noticing some parts issues.
2025-06-09 Adjust notes on SCH
2025-06-09 Update SCH PDF
2025-06-10 Change FB array resistors
    Change FB resistor values for step down converter, changing output voltage to be much closer to 5V.
    Footprint of resistors changed.
2025-06-11 Adjust PCB silkscreen text
2025-06-11 Create production files
2025-06-18 Prepare for V1.0 production
    Export fab files for PCB manufacturing and parts ordering
2025-07-09 PCB version 1.1 following peer review
    PTC in line with live, previously shorted between live and neutral.
    Added boxes around sections on schematic for better readability.
    Modified terminal block silkscreen to make more sense
    Modified routing of 5V power to to reduce tunnels and traces on bottom plane.
2025-07-11 Continue V1.1 modifications
    Round off corners on PCB
    Remove solder mount for triacs, unnecessary addition. Can use adhesive if required to secure triacs.
    Remove unnecessary vias between top and bottom ground planes
2025-07-12 Change SMPS voltage divider
    Somehow managed to miscalculate the voltage divider resistor values to get 5V, getting 7V.
    Change resistor values, change to 0805 footprint.
2025-07-12 Fix LED outputs and GPIO assignments
    Get LED outputs working correctly, fix GPIO assignments to match PCB
2025-07-14 Update PCB and SCH for snubber circuit DNF
    Snubber circuit is drawing too much power, capacitor and resistor values need to be looked at.
    Not including the circuit for the time being.
    Added alternate part for resistor, 0 ohm jumper.
    DNF capacitor in snubber circuit for each output.
2025-10-03 Begin working on V1.1
    Starting to add additional features.
    Coming up:
    Make sprinkler component valve and pump settings adjustable.
    Add a "skip next planned day" toggle switch
2025-10-03 Remove ID prefix substitution
    Remove prefix substitution, pointless.
2025-10-29 Update README.md
    Make it clear the readme is outdated and not finished
2026-01-04 WIFI LED logic and logging
    Fixed WIFI LED logic
    Minor spacing and wording changes
2026-01-04 Delete PCB/ESPrinkler Retic PCB/production directory
    Multiple folder names, case sensitive apparently
2026-01-04 Migrate settings and controls to config section
    Set anything relating to config to be as such so the entity loads as "config". Reduces items in "Control".
2026-01-04 Fix pause feature
    Change "start" button to resume_or_start_full_cycle so that pause feature will work correctly
2026-01-04 Move Main Start/Stop
    Had the main start/stop button moved to config, but makes more sense to keep it under controls
2026-04-07 Update retic-controller.yaml
    Made all zone switches internal only
    Change comment for "internal: True".
2026-04-07 Update retic-controller.yaml
    Make auto advance switch for their respective program internal.
2026-04-07 Update retic-controller.yaml
    Change all logins and authentication to secrets
2026-04-07 Create secrets.yaml
    Add example secrets.yaml file
2026-05-01 Remove snubber and bring Kicad V10 update
    Remove snubber from triac driver as its not required.
    Attempt to start migrating to Kicad V10
2026-05-09 Clean up schematic
    Layout schematic a bit better
2026-05-09 Change DC-DC converter & PCB routing
    Previous DC-DC converter max input voltage was close to VIN. Changed out for 40V rated input, and a simpler design.
    Also re-routed 5V rail to top layer to reduce layer swapping using vias for power lines
2026-05-09 Add TVS protection
    Added SMAJ33A TVS on VCC
2026-05-09 Start updating models
    Updating models since moving to kicad 10.
    Will begin migrating to project library entirely
2026-05-10 Labelling as V2.0
    Repo needs to change, I have been using it poorly. V2.0 will be the next "main branch". After that, forks will be used instead
    Also in this commit, I have updated the custom footprints and updated the links to them in the project.
2026-05-11 Change 12-pin connector
    Change from screw terminal barrier block to a wire-to-board screw terminal block.
    Opted for a 3-pin terminal block, 4 of them due the 12-pin not being available through lcsc, to get a total of 12 when connected together. Makes the design a bit confusing but the BOM is accurate
2026-05-12 Change mounting holes
    Change mounting holes to M3.2 with exposed pads and vias. Add them to schematic for reference
2026-05-19 Update secrets.yaml
    Fix syntax mistakes
2026-05-19 Delete LICENSE
    Change license
2026-05-19 Create LICENSE
    GPLv3
2026-05-20 Update README.md
    Start making the readme
2026-05-20 Update README.md
    Continue updating README
2026-05-23 Add ESPrinkler configuration dashboard example
2026-05-23 Update README.md
    Gave GPT my specs doc to help write this readme, make some changes to the output it spat out
2026-05-23 Delete PCB/ESPrinkler Retic PCB/Production directory
    Moving production files up one, keeping it out of the PCB project directory
2026-05-23 Edit BOM and silkscreen
    Getting ready to make production files
2026-05-24 Production File Test
    Export all files required for JLCPCB production.
    Included in this commit is a minor change to Zone 8 triac output trace run.
2026-05-24 PCB properties
    Save properties
2026-05-24 Complete production files
    Production files correct for JLCPCB & LCSC.
    Delete raw files, keep compressed production file.
2026-05-24 Modifications after Reddit review
    Changes made to design following reddit review (thank you everyone who gave their input!)
    Changed rectifier reservoir cap to 470uF, added 2nd one just in case its needed.
    Changed all TH caps to polymer type.
    Adjusted schematic and PCB layout
    Delete production files, working on new ones.
2026-05-25 Create new production file
    Create compresses folder with all production files
2026-05-25 Change framework to ESP-IDF
    Changed framwork from Arduino to ESP-IDF.
    Required the change of some functions using "String()" as its not supported.
    Compiles, requires testing
2026-05-25 Update README.md
    Update with a section for known bugs and limitations.
    Include the time and date setting issue in this section
2026-05-28 Update retic-controller.yaml
    Removed a comment
2026-06-14 Add 3D model for DevKit C board
